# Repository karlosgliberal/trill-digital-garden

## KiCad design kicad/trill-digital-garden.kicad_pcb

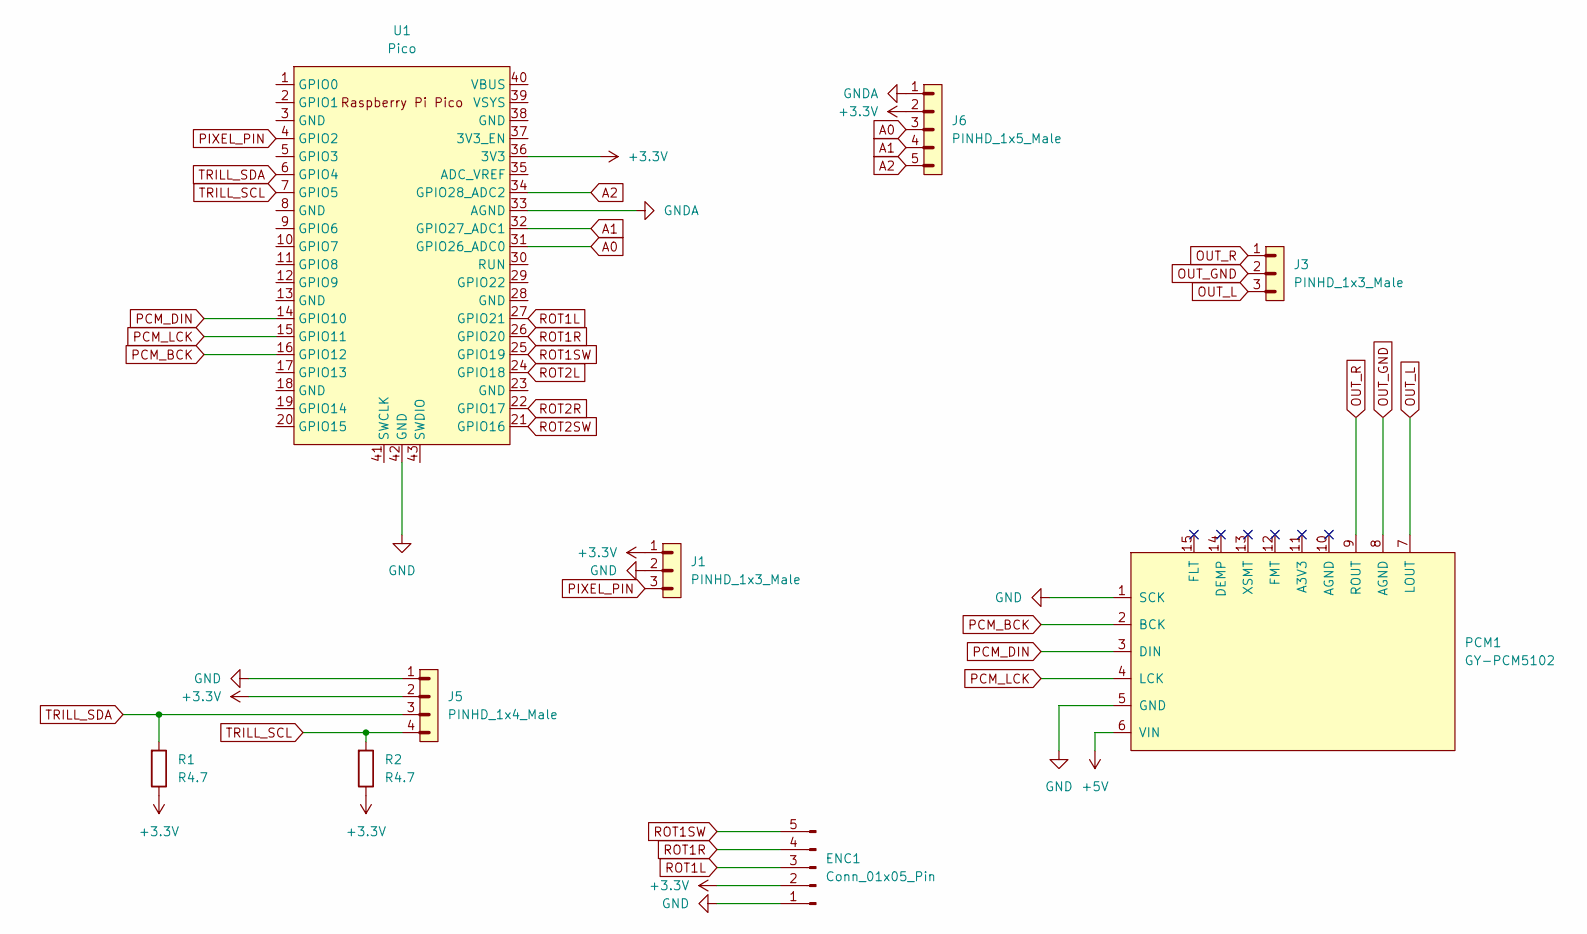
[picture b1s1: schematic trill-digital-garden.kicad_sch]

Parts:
ENC1: Conn_01x05_Pin; JST_EH_B5B-EH-A_1x05_P2.50mm_Vertical
J1, J3: PINHD_1x3_Male; JST_EH_B3B-EH-A_1x03_P2.50mm_Vertical
J5: PINHD_1x4_Male; PinHeader_1x04_P2.54mm_Vertical
J6: PINHD_1x5_Male; JST_EH_B5B-EH-A_1x05_P2.50mm_Vertical
PCM1: GY-PCM5102
R1, R2: R4.7; R_Axial_DIN0207_L6.3mm_D2.5mm_P7.62mm_Horizontal
U1: Pico; RPi_Pico_SMD_TH

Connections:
+3.3V: ENC1.2, J1.1, J5.2, J6.2, R1.2, R2.2, U1.36 (3V3)
+5V: PCM1.6 (VIN)
A0: J6.3, U1.31 (GPIO26_ADC0)
A1: J6.4, U1.32 (GPIO27_ADC1)
A2: J6.5, U1.34 (GPIO28_ADC2)
GND: ENC1.1, J1.2, J5.1, PCM1.1 (SCK), PCM1.5 (GND), U1.42 (GND)
GNDA: J6.1, U1.33 (AGND)
OUT_GND: J3.2, PCM1.8 (AGND)
OUT_L: J3.3, PCM1.7 (LOUT)
OUT_R: J3.1, PCM1.9 (ROUT)
PCM_BCK: PCM1.2 (BCK), U1.16 (GPIO12)
PCM_DIN: PCM1.3 (DIN), U1.14 (GPIO10)
PCM_LCK: PCM1.4 (LCK), U1.15 (GPIO11)
PIXEL_PIN: J1.3, U1.4 (GPIO2)
ROT1L: ENC1.3, U1.27 (GPIO21)
ROT1R: ENC1.4, U1.26 (GPIO20)
ROT1SW: ENC1.5, U1.25 (GPIO19)
ROT2L: U1.24 (GPIO18)
ROT2R: U1.22 (GPIO17)
ROT2SW: U1.21 (GPIO16)
TRILL_SCL: J5.4, R2.1, U1.7 (GPIO5)
TRILL_SDA: J5.3, R1.1, U1.6 (GPIO4)

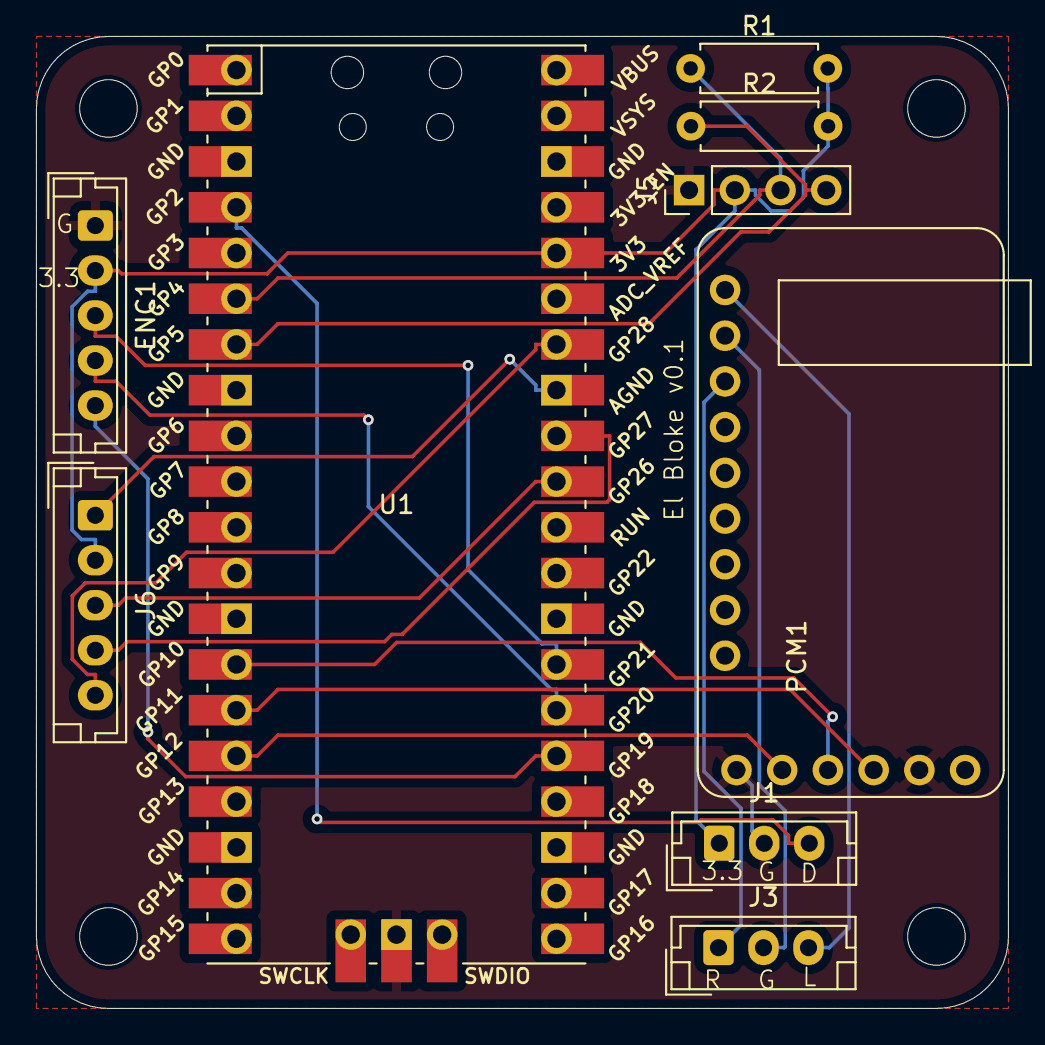
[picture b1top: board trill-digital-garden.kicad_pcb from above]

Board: 2 copper layers, 54.0 x 54.0 mm, 13 parts (0 on the bottom side), 18 nets.

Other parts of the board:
M1, M2, M3, M4: MountingHole_3.2mm_M3

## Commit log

2025-03-04 :seedling: First seeds for the garden
2025-03-04 :memo: Readme
